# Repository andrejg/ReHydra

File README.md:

# ReHydra
An adaptation of the Hydra network card for Atari ST/TT/Falcon series of computers, making it work with obtainable modern RJ45 jacks like Hanrun HR911105A.

The original design (https://www.atariworld.org/hardware/hydra/) was done by Mathias Münch in 2009 and published under Attribution-NonCommercial-ShareAlike 4.0.

This rework is published under the same license.

https://creativecommons.org/licenses/by-nc-sa/4.0/legalcode.txt

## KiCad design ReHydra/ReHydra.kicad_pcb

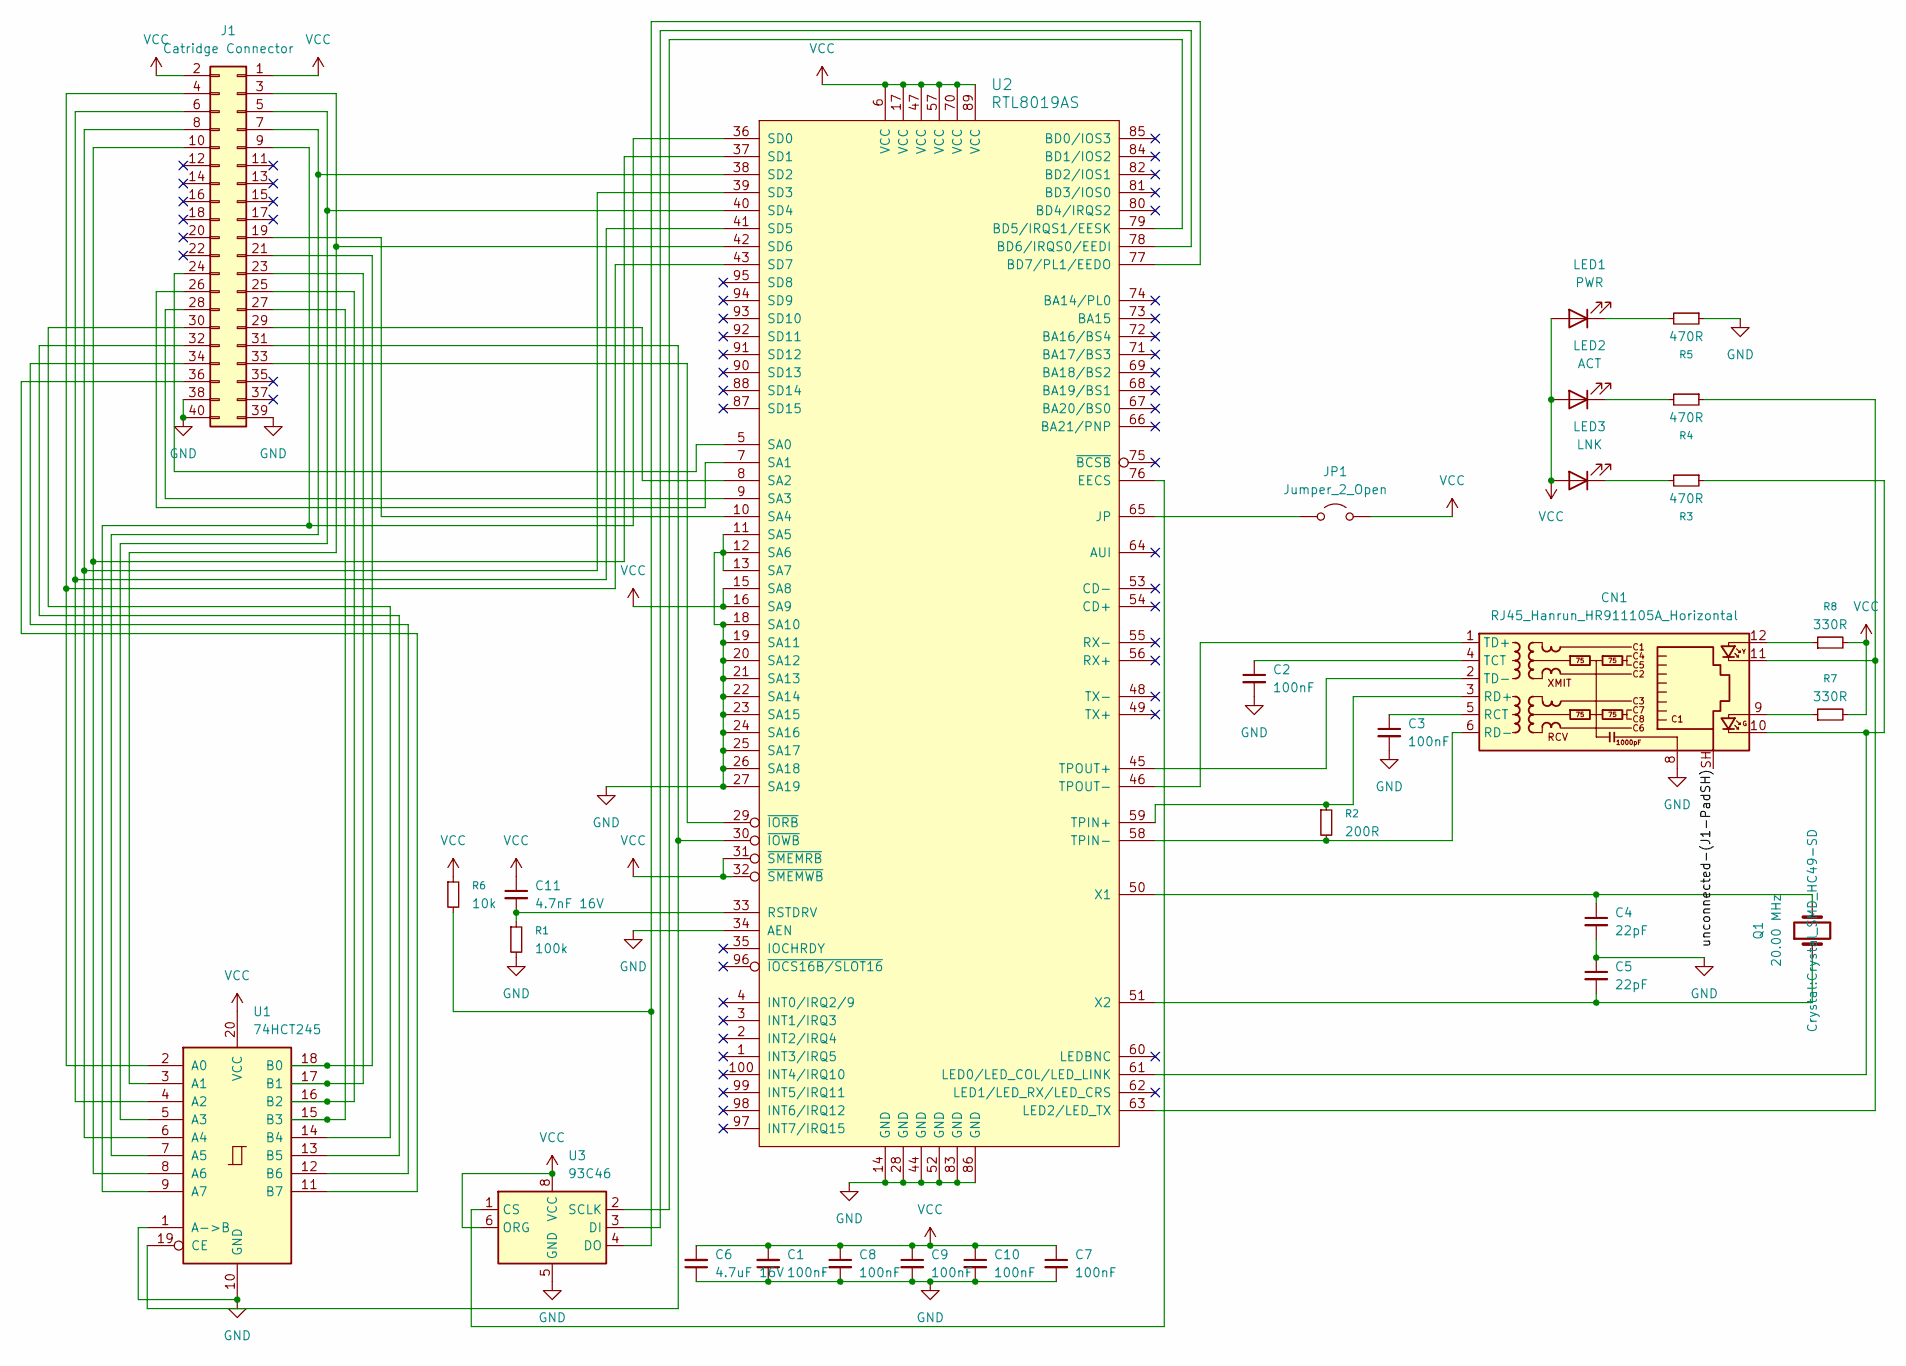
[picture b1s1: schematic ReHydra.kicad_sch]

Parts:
C1, C2, C3, C7, C8, C9, C10: 100nF; C_0805_2012Metric
C4, C5: 22pF; C_0805_2012Metric
C6: 4.7uF 16V; C_0805_2012Metric
C11: 4.7nF 16V; C_0805_2012Metric
CN1: RJ45_Hanrun_HR911105A_Horizontal
J1: Catridge Connector; Cartridge Connector
JP1: Jumper_2_Open; R_0805_2012Metric
LED1: PWR; LED_0805_2012Metric
LED2: ACT; LED_0805_2012Metric
LED3: LNK; LED_0805_2012Metric
Q1: 20.00 MHz; Crystal_SMD_HC49-SD
R1: 100k; R_0805_2012Metric
R2: 200R; R_0805_2012Metric
R3, R4, R5: 470R; R_0805_2012Metric
R6: 10k; R_0805_2012Metric
R7, R8: 330R; R_0805_2012Metric
U1: 74HCT245; Infineon_SOIC-20W_7.6x12.8mm_P1.27mm
U2: RTL8019AS; PQFP-100
U3: 93C46; SOIC-8_3.9x4.9mm_P1.27mm

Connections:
/unconnected-(J1-PadSH): CN1.SH
GND: C1.1, C2.2, C3.2, C4.2, C5.1, C6.1, C7.2, C8.2, C9.2, C10.2, CN1.8, J1.38, J1.39, J1.40, R1.2, R5.1, U1.1 (A->B), U1.10 (GND), U2.11 (SA5), U2.12 (SA6), U2.13 (SA7), U2.14 (GND), U2.18 (SA10), U2.19 (SA11), U2.20 (SA12), U2.21 (SA13), U2.22 (SA14), U2.23 (SA15), U2.24 (SA16), U2.25 (SA17), U2.26 (SA18), U2.27 (SA19), U2.28 (GND), U2.34 (AEN), U2.44 (GND), U2.52 (GND), U2.83 (GND), U2.86 (GND), U3.5 (GND)
unnamed: CN1.9, R7.1
unnamed: CN1.12, R8.1
unnamed: C3.1, CN1.5 (RCT)
unnamed: CN1.3 (RD+), R2.1, U2.59 (TPIN+)
unnamed: CN1.6 (RD-), R2.2, U2.58 (TPIN-)
unnamed: C2.1, CN1.4 (TCT)
unnamed: CN1.1 (TD+), U2.46 (TPOUT-)
unnamed: CN1.2 (TD-), U2.45 (TPOUT+)
unnamed: J1.3, U1.3 (A1), U2.42 (SD6)
unnamed: J1.4, U1.2 (A0), U2.43 (SD7)
unnamed: J1.5, U1.5 (A3), U2.40 (SD4)
unnamed: J1.6, U1.4 (A2), U2.41 (SD5)
unnamed: J1.7, U1.7 (A5), U2.38 (SD2)
unnamed: J1.8, U1.6 (A4), U2.39 (SD3)
unnamed: J1.9, U1.9 (A7), U2.36 (SD0)
unnamed: J1.10, U1.8 (A6), U2.37 (SD1)
unnamed: J1.19, U2.10 (SA4)
unnamed: J1.21, U1.18 (B0)
unnamed: J1.23, U1.17 (B1)
unnamed: J1.24, U2.5 (SA0)
unnamed: J1.25, U1.16 (B2)
unnamed: J1.26, U2.7 (SA1)
unnamed: J1.27, U1.15 (B3)
unnamed: J1.28, U2.9 (SA3)
unnamed: J1.29, U2.8 (SA2)
unnamed: J1.30, U1.14 (B4)
unnamed: J1.31, U1.19 (CE), U2.30 (~IOWB)
unnamed: J1.32, U1.13 (B5)
unnamed: J1.33, U2.29 (~IORB)
unnamed: J1.34, U1.12 (B6)
unnamed: J1.36, U1.11 (B7)
unnamed: JP1.1 (A), U2.65 (JP)
unnamed: LED1.1 (K), R5.2
unnamed: LED2.1 (K), R4.2
unnamed: LED3.1 (K), R3.2
unnamed: U2.79 (BD5/IRQS1/EESK), U3.2 (SCLK)
unnamed: U2.78 (BD6/IRQS0/EEDI), U3.3 (DI)
unnamed: R6.2, U2.77 (BD7/PL1/EEDO), U3.4 (DO)
unnamed: U2.76 (EECS), U3.1 (CS)
unnamed: CN1.10, R3.1, U2.61 (LED0/LED_COL/LED_LINK)
unnamed: CN1.11, R4.1, U2.63 (LED2/LED_TX)
unnamed: C11.2, R1.1, U2.33 (RSTDRV)
unnamed: C4.1, Q1.2, U2.50 (X1)
unnamed: C5.2, Q1.1, U2.51 (X2)
VCC: C1.2, C6.2, C7.1, C8.1, C9.1, C10.1, C11.1, J1.1, J1.2, JP1.2 (B), LED1.2 (A), LED2.2 (A), LED3.2 (A), R6.1, R7.2, R8.2, U1.20 (VCC), U2.6 (VCC), U2.15 (SA8), U2.16 (SA9), U2.17 (VCC), U2.31 (~SMEMRB), U2.32 (~SMEMWB), U2.47 (VCC), U2.57 (VCC), U2.70 (VCC), U2.89 (VCC), U3.6 (ORG), U3.8 (VCC)

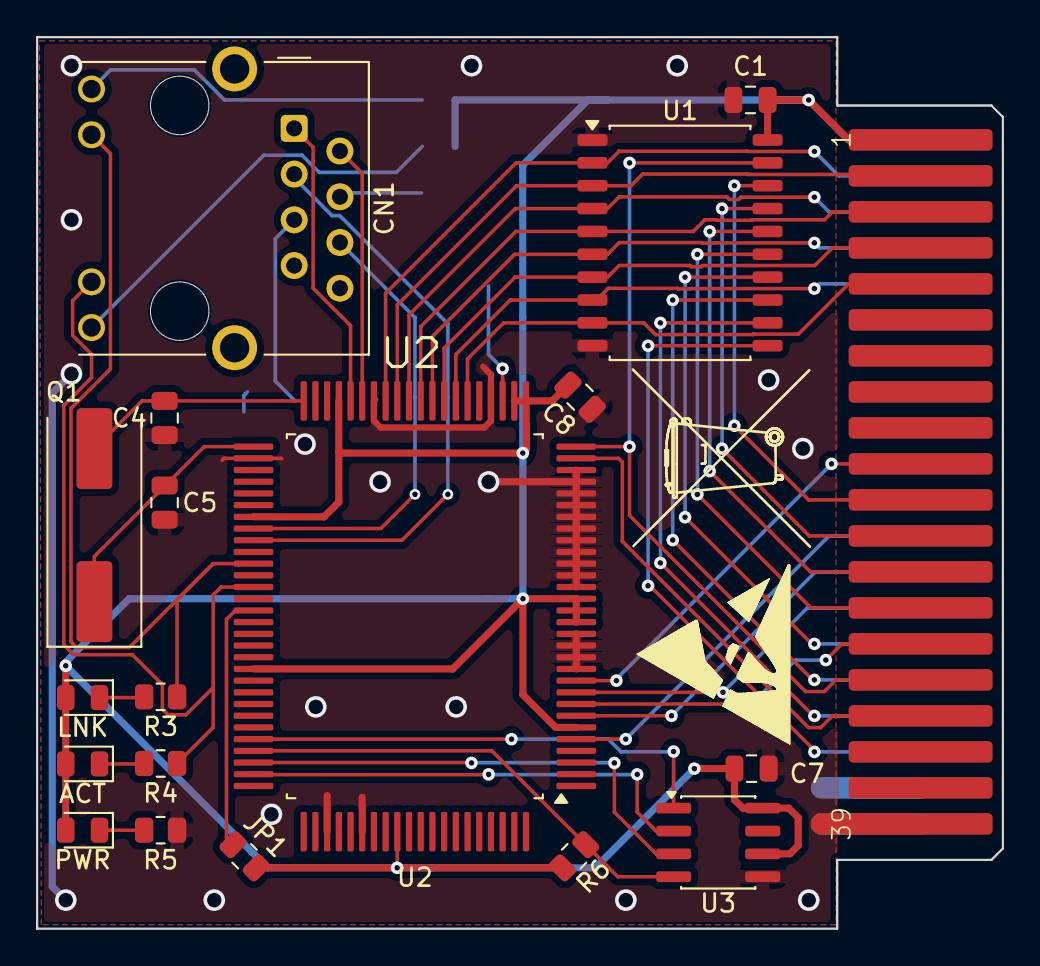
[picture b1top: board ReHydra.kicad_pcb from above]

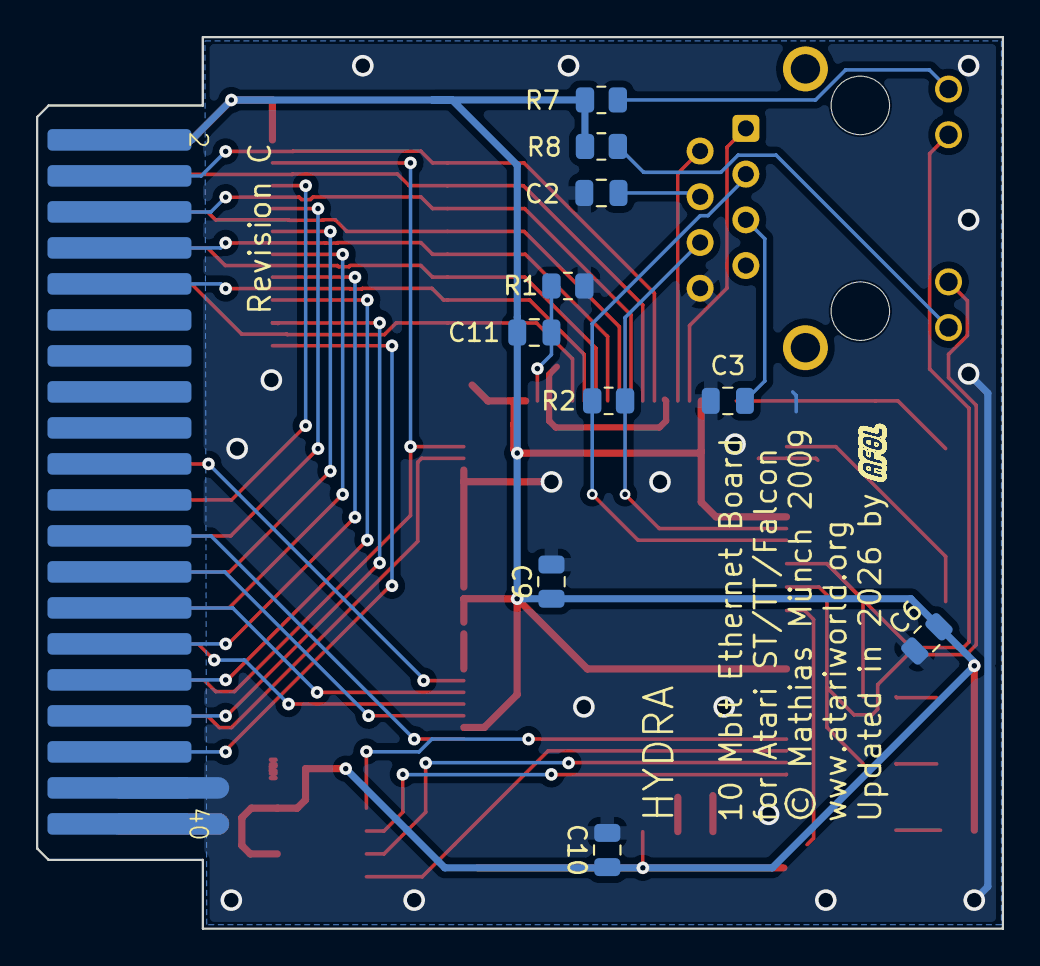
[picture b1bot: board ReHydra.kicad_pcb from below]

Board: 2 copper layers, 53.7 x 49.5 mm, 29 parts (10 on the bottom side), 46 nets.

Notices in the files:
ReHydra/ReHydra.kicad_pcb:
© Mathias Münch 2009
